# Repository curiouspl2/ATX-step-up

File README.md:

# ATX-step-up
DC DC step up driver turning flaky and sagging ATX power supply to stable 14V or 24V source

One can also use it to 'parallel' power supplies - just connect each power supply to separate input. 

v3 version supports four inputs, rated 10-20A each (depends on heatsinking and mosfets used).

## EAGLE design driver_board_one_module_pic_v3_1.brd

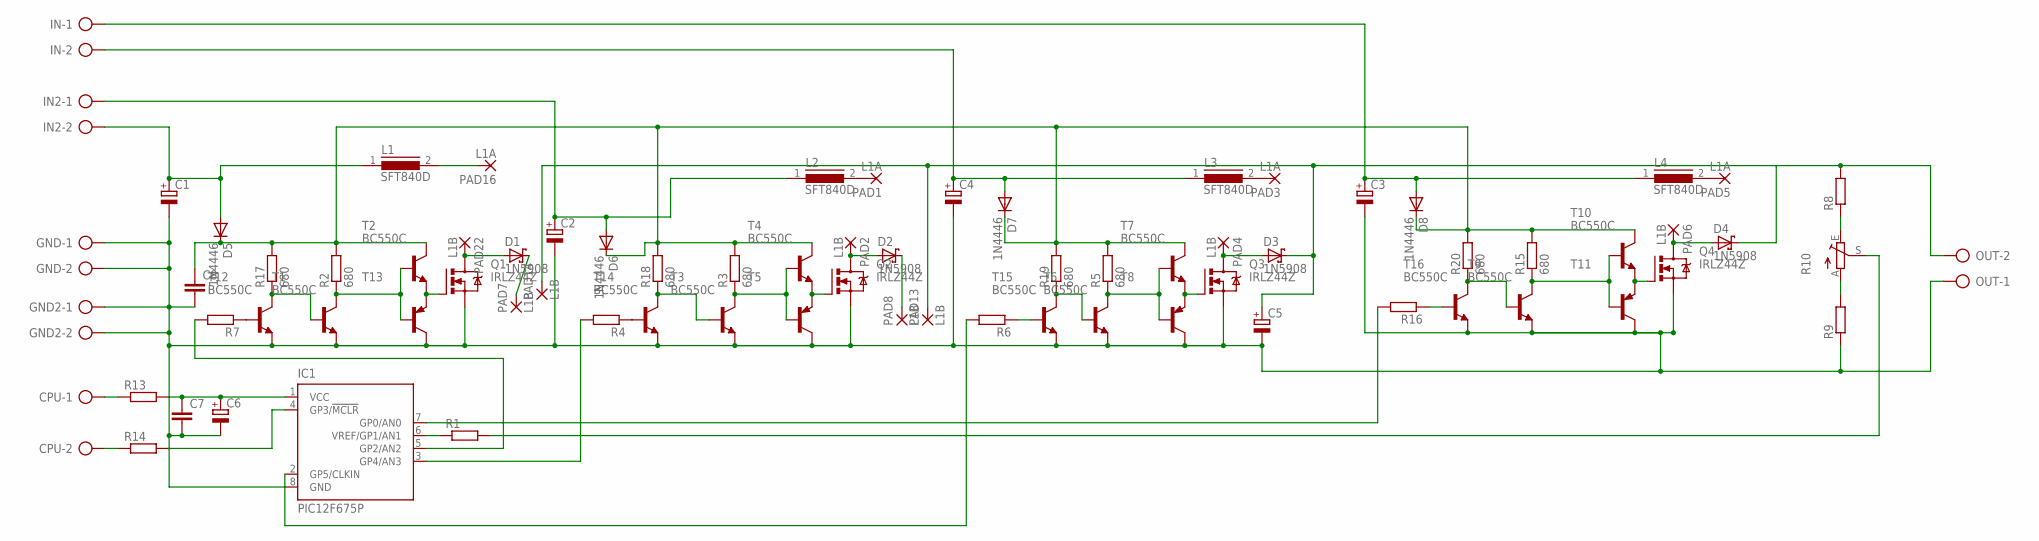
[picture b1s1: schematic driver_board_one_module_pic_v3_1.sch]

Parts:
C1, C2, C3, C4, C5, C6: CPOL-EUE5-8.5; E5-8,5
C7: C-EUC1206K; C1206K
C8: C-EU050-045X075; C050-045X075
CPU: AK300/2
D1, D2, D3, D4: 1N5908; C4111-15
D5, D6, D7, D8: 1N4446; DO35-10
GND, GND2: AK300/2
IC1: PIC12F675P; DIL8
IN, IN2: AK300/2
L1, L2, L3, L4: SFT840D
OUT: AK300/2
PAD1, PAD3, PAD5, PAD16: L1A; 3,81/1,1
PAD2, PAD4, PAD6, PAD7, PAD8, PAD13, PAD14, PAD22: L1B; 3,81/1,1
Q1, Q2, Q3, Q4: IRLZ44Z; TO220BH
R1, R8, R9, R13, R14: R-EU_0204/5; 0204/5
R2: 680; 0207/7
R3, R5, R15, R17, R18, R19, R20: 680; 0204/5
R4: R-EU_0207/7; 0207/7
R6, R7: R-EU_0207/12; 0207/12
R10: TRIM_EU-RJ9W; RJ9W
R16: R-EU_0207/10; 0207/10
T1, T2, T3, T4, T6, T7, T9, T10, T12, T14, T15, T16: BC550C; TO92-EBC
T5, T8, T11, T13: BC557C-PNP-TO92-EBC; TO92-EBC

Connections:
GND: C1.-, C2.-, C3.-, C4.-, C5.-, C6.-, C7.2, C8.2, GND.1, GND.2, GND2.1, GND2.2, IC1.8 (GND), OUT.1, Q1.S, Q2.S, Q3.S, Q4.S, R9.1, T1.E, T3.E, T5.C, T6.E, T8.C, T9.E, T11.C, T12.E, T13.C, T14.E, T15.E, T16.E
unnamed: Q1.G, T2.E, T13.E
unnamed: IC1.7 (GP0/AN0), R16.2
unnamed: Q2.G, T4.E, T5.E
unnamed: CPU.1, R13.1
unnamed: R9.2, R10.A
unnamed: R6.1, T15.B
unnamed: CPU.2, R14.1
unnamed: D2.A, PAD2.1, Q2.D
unnamed: R8.1, R10.E
unnamed: L2.2, PAD1.1
unnamed: Q3.G, T7.E, T8.E
unnamed: Q4.G, T10.E, T11.E
unnamed: R7.1, T12.B
unnamed: R1.2, R10.S
unnamed: R17.1, T1.B, T12.C
unnamed: D3.A, PAD4.1, Q3.D
unnamed: R4.1, T14.B
unnamed: R18.1, T3.B, T14.C
unnamed: L3.2, PAD3.1
unnamed: IC1.5 (GP2/AN2), R7.2
unnamed: IC1.3 (GP4/AN3), R4.2
unnamed: IC1.2 (GP5/CLKIN), R6.2
unnamed: C6.+, C7.1, IC1.1 (VCC), R13.2
unnamed: IC1.4 (GP3/!MCLR), R14.2
unnamed: IC1.6 (VREF/GP1/AN1), R1.1
unnamed: C1.+, D5.A, IN2.2, L1.1
unnamed: C2.+, D6.A, IN2.1, L2.1
unnamed: C4.+, D7.A, IN.2, L3.1
unnamed: D1.C, PAD7.1
unnamed: R16.1, T16.B
unnamed: L1.2, PAD16.1
unnamed: D1.A, PAD22.1, Q1.D
unnamed: R2.1, T1.C, T2.B, T13.B
unnamed: D4.A, PAD6.1, Q4.D
unnamed: L4.2, PAD5.1
unnamed: R3.1, T3.C, T4.B, T5.B
unnamed: C3.+, D8.A, IN.1, L4.1
unnamed: R5.1, T6.C, T7.B, T8.B
unnamed: R15.1, T9.C, T10.B, T11.B
unnamed: R19.1, T6.B, T15.C
unnamed: R20.1, T9.B, T16.C
unnamed: D2.C, PAD8.1
unnamed: C8.1, D5.C, D6.C, D7.C, D8.C, R2.2, R3.2, R5.2, R15.2, R17.2, R18.2, R19.2, R20.2, T2.C, T4.C, T7.C, T10.C
unnamed: C5.+, D3.C, D4.C, OUT.2, PAD13.1, PAD14.1, R8.2

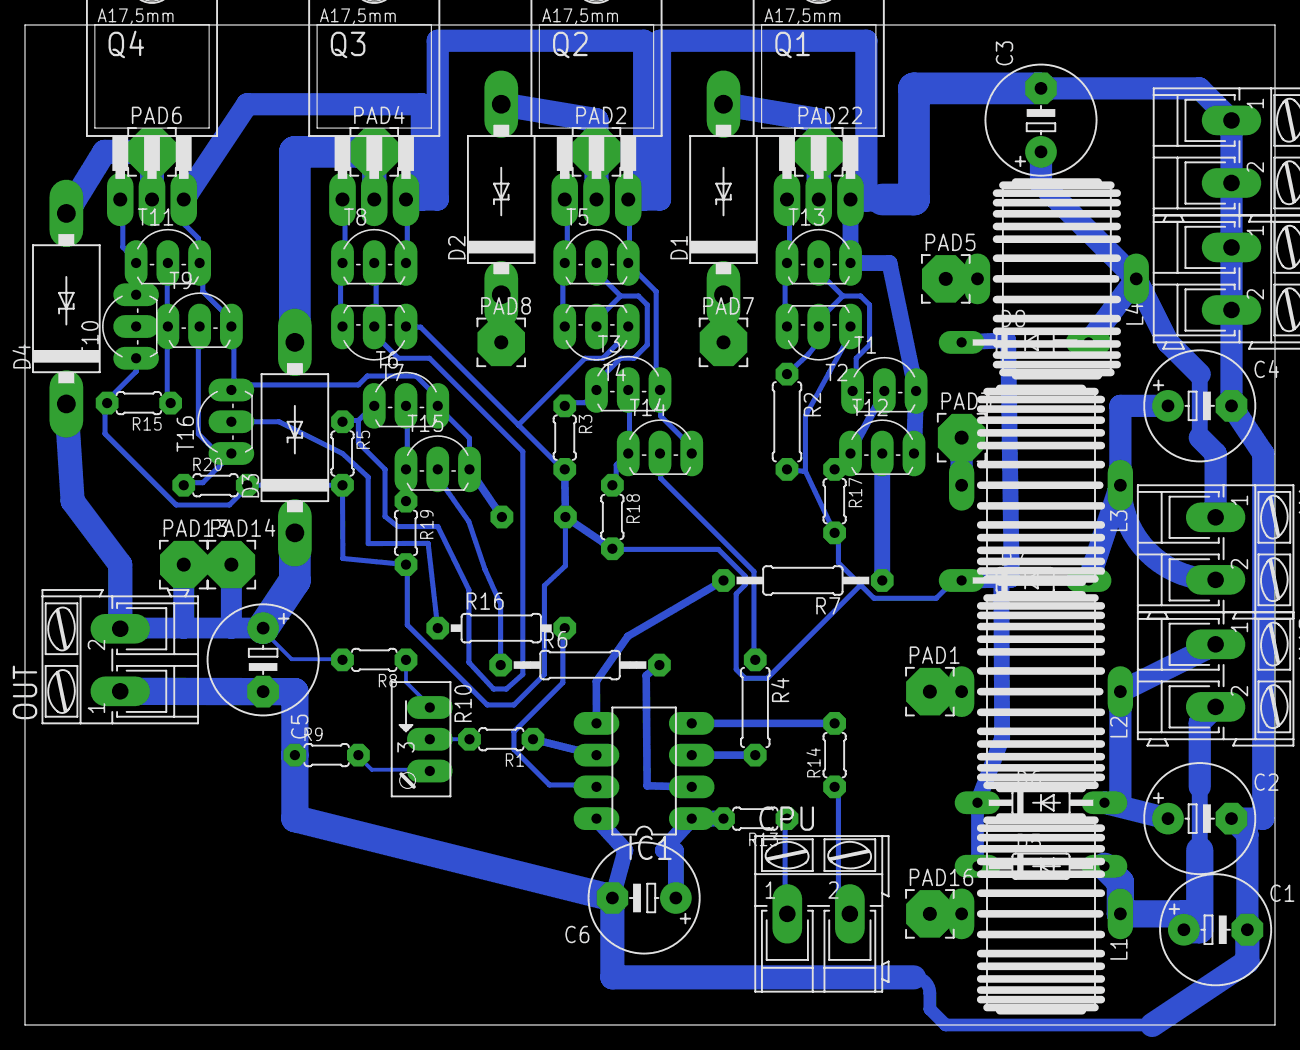
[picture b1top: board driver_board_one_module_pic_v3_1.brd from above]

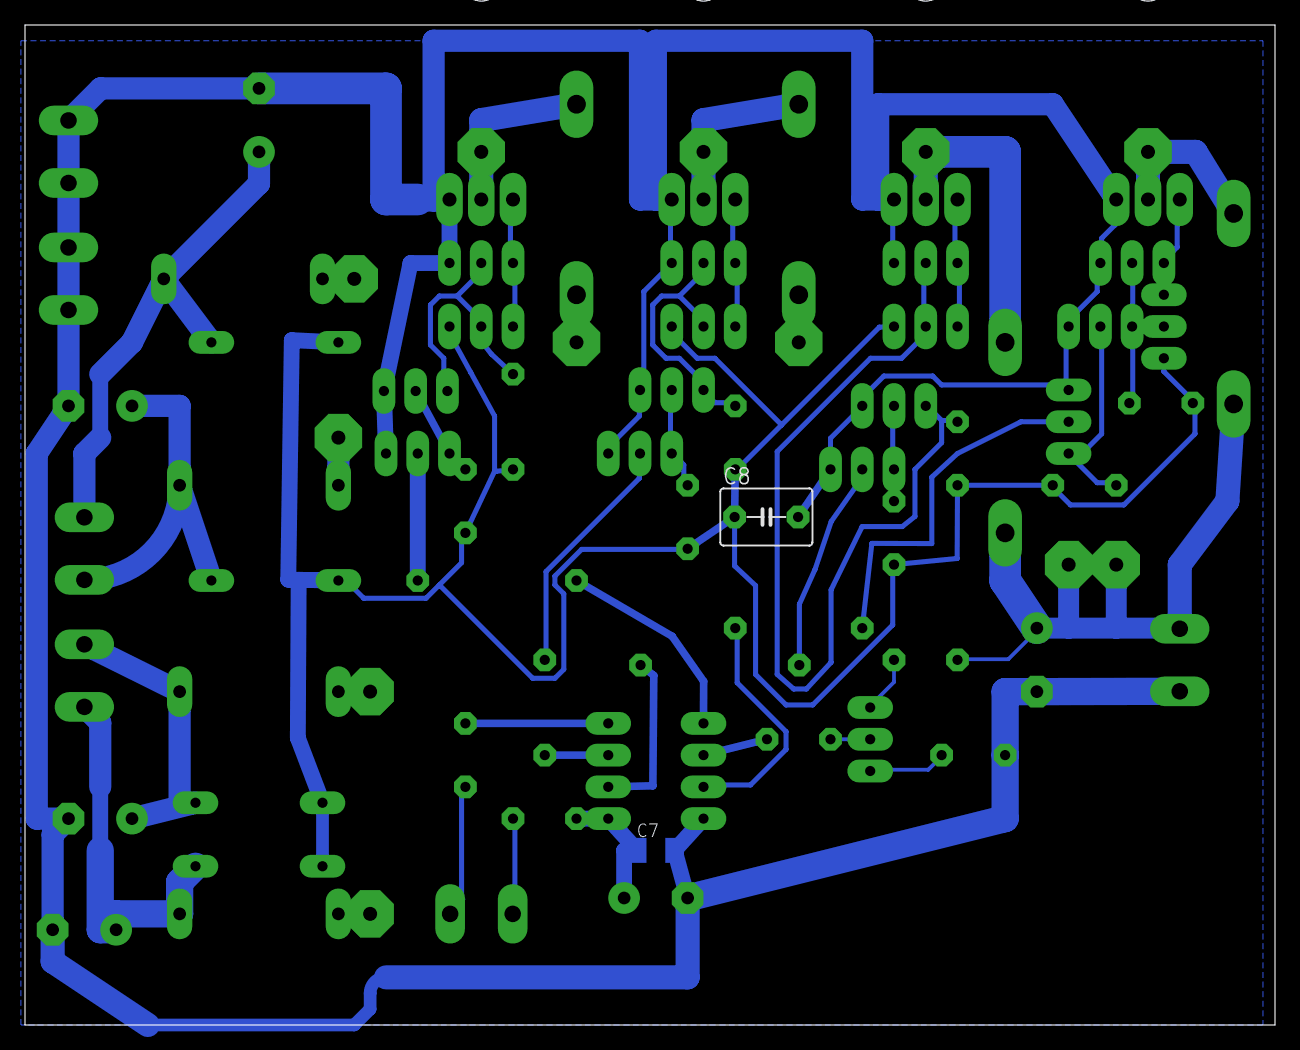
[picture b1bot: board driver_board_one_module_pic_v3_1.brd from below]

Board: 2 copper layers, 100.0 x 80.0 mm, 77 parts (2 on the bottom side), 45 nets.

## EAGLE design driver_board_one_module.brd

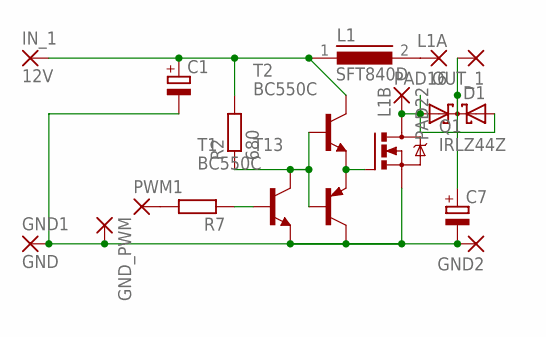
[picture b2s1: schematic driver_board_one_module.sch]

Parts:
C1, C7: CPOL-EUE5-8.5; E5-8,5
D1: DIODE_2SCHOTTKY-SOT93V; SOT93S
GND1: GND; 3,81/1,3
GND2: 3,81/1,3
GND_PWM: 2,54/0,8
IN_1: 12V; 3,81/1,3
L1: SFT840D
OUT_1: 3,81/1,3
PAD16: L1A; 3,81/1,1
PAD22: L1B; 3,81/1,1
PWM1: 2,54/0,8
Q1: IRLZ44Z; TO220BH
R2: 680; 0204/7
R7: R-EU_0207/7; 0207/7
T1, T2: BC550C; TO92-EBC
T13: BC557C-PNP-TO92-EBC; TO92-EBC

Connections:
unnamed: Q1.G, T2.E, T13.E
unnamed: R2.1, T1.C, T2.B, T13.B
unnamed: C1.-, C7.-, GND1.1, GND2.1, GND_PWM.1, Q1.S, T1.E, T13.C
unnamed: PWM1.1, R7.2
unnamed: R7.1, T1.B
unnamed: C1.+, IN_1.1, L1.1, R2.2, T2.C
unnamed: L1.2, PAD16.1
unnamed: D1.A1, D1.A2, PAD22.1, Q1.D
unnamed: C7.+, D1.C, OUT_1.1

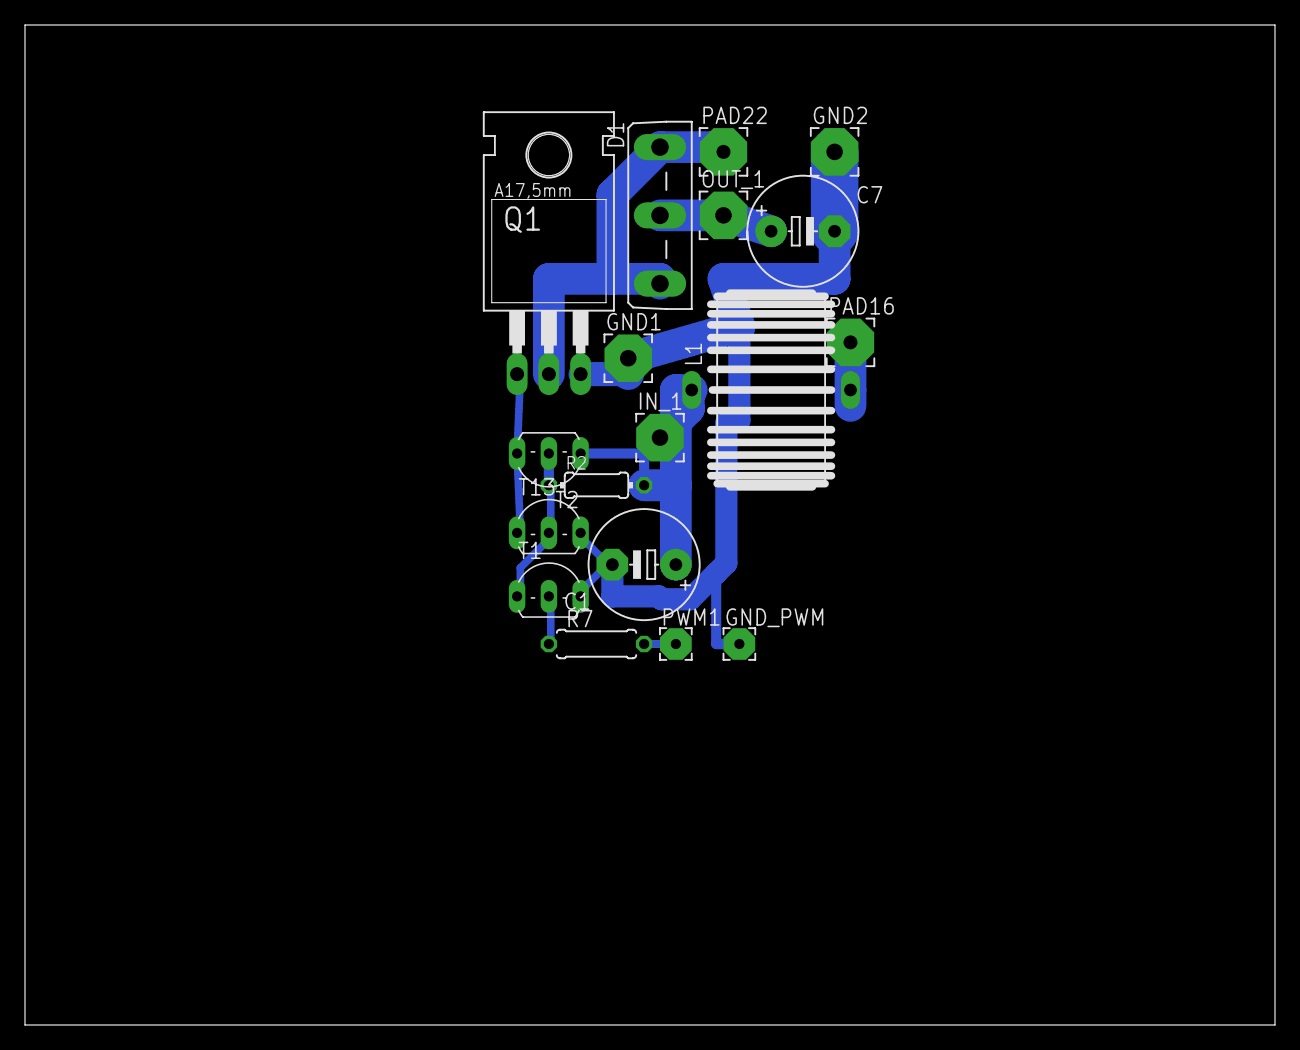
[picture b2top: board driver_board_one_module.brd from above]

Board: 2 copper layers, 100.0 x 80.0 mm, 18 parts (0 on the bottom side), 9 nets.

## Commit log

2017-08-20 Add files via upload
    changed layout from 0 active to active 1 to prevent lockups and make everything more secure.
    improved code efficiency.
    board is now tested , switching about 1A per phase without any heatsinking and around 5A-10A per phase with small heatsink.
    todo : irfz44 sucks. at least four of them are needed to switch 10-20A range of current and staying cool.
    up to four are still cost-effective though vs other mosfets. perhaps adding some cheap bipolar transistors to speed up turn on and turn-off times would make sense?
